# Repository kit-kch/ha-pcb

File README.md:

# KCH Half Adder PCB

This repository contains schematic, layout and BOM for the KCH half adder PCB.
The PCB realizes a half adder using NAND gates, where some of the on-board components are left to be soldered by students as an exercise.

Multiple PCBs can be connected to each other to form full adders or multi-bit carry ripple adders.
In addition to the PCB, we provide detailed documentation explaining the theory involved for both the PCB design and the digital circuit realization.

As the intended target audience is school students and their teachers, documentation is currently only available in German.

## Ordering the PCBs

The initial batch of boards we have successfully used in a workshop has been ordered using JLCPCB's standard assembly service.
We had all the parts assembled, except for the switches and the 74HC00 ICs that are marked as do-not-place in the schematic.
Because of that, both-sided assembly and THT assembly is required.
The files we used to order from JLCPCB can be found in the production folder.

Please note: As the connectors are overlapping, the assembly service needs to add some spacers when paneling the design. Either panel yourself or let the factory know about this requirement.

Please also note that the boards should align when connected together.
PCB edges therefore need to be smooth so mouse bites should not be used.
Make sure to use v-score / v-cut panels instead.

## More Information and Documentation

* Project Website and Documentation: [kch.dev/ha](https://kch.dev/ha)
* Project Schematic: [kch_ha.pdf](kch_ha.pdf)

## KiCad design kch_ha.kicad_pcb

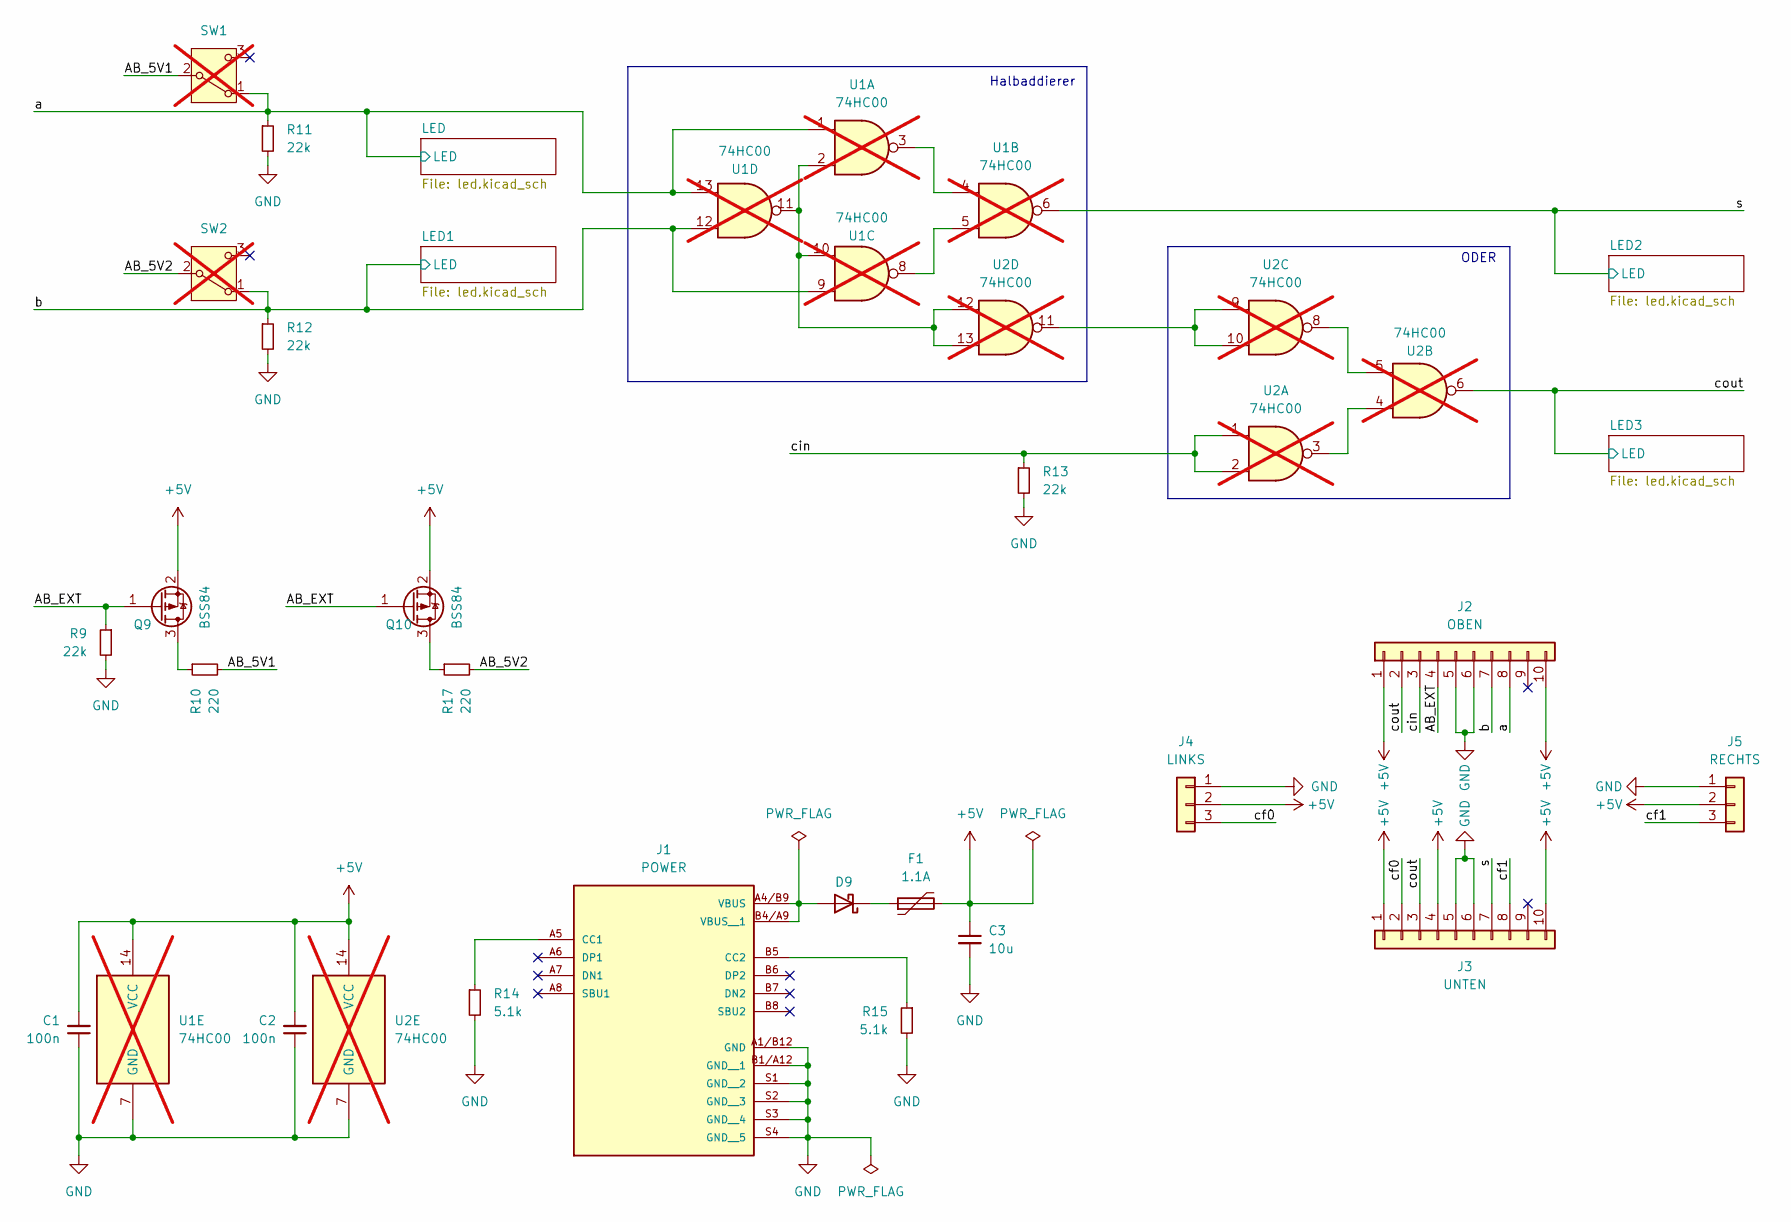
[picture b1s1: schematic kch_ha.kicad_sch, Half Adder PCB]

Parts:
C1, C2: 100n; C_0805_2012Metric; LCSC C476766
C3: 10u; C_0805_2012Metric; LCSC C5137471
D9: D_SMA; LCSC C2844169
F1: 1.1A; FUSER_2016L050MR; MPN 2016L050MR; LCSC C99564
J1: POWER; GCT_USB4110-GF-A_REVB; PARTREV B; LCSC C5143397
J2: OBEN; PinSocket_1x10_P2.54mm_Horizontal; MPN PPTC101LGBN-RC; LCSC C22438151
J3: UNTEN; PinHeader_1x10_P2.54mm_Horizontal; MPN PH1RB-10-UA; LCSC C492418
J4: LINKS; PinHeader_1x03_P2.54mm_Horizontal; MPN PH1RB-03-UA; LCSC C492411
J5: RECHTS; PinSocket_1x03_P2.54mm_Horizontal; MPN PPTC031LGBN-RC; LCSC C22438144
Q9, Q10: BSS84; SOT-23; MPN BSS84P; LCSC C112238
R9, R11, R12, R13: 22k; R_0805_2012Metric; LCSC C139902
R10, R17: 220; R_0805_2012Metric; LCSC C2933537
R14, R15: 5.1k; R_0805_2012Metric; LCSC C2930296
SW1: a; SW_Slide-03_Wuerth-WS-SLTV_10x2.5x6.4_P2.54mm; not fitted
SW2: b; SW_Slide-03_Wuerth-WS-SLTV_10x2.5x6.4_P2.54mm; not fitted
U1, U2: 74HC00; DIP-14_W7.62mm; MPN 74HC00; not fitted

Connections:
+5V: C1.2, C2.2, C3.1, F1.2, J2.1, J2.10, J3.1, J3.4, J3.10, J4.2, J5.2, Q9.2 (S), Q10.2 (S), U1.14 (VCC), U2.14 (VCC); also elsewhere on the board
/AB_5V1: R10.2, SW1.2 (B)
/AB_5V2: R17.2, SW2.2 (B)
/AB_EXT: J2.4, Q9.1 (G), Q10.1 (G), R9.1
/a: J2.8, R11.1, SW1.1 (A), U1.1, U1.13; also elsewhere on the board
/b: J2.7, R12.1, SW2.1 (A), U1.9, U1.12; also elsewhere on the board
/cf0: J3.2, J4.3
/cf1: J3.8, J5.3
/cin: J2.3, R13.1, U2.1, U2.2
/cout: J2.2, J3.3, U2.6; also elsewhere on the board
/s: J3.7, U1.6; also elsewhere on the board
GND: C1.1, C2.1, C3.2, J1.A1/B12 (GND), J1.B1/A12 (GND__1), J1.S1 (GND__2), J1.S2 (GND__3), J1.S3 (GND__4), J1.S4 (GND__5), J2.5, J2.6, J3.5, J3.6, J4.1, J5.1, R9.2, R11.2, R12.2, R13.2, R14.2, R15.2, U1.7 (GND), U2.7 (GND); also elsewhere on the board
unnamed: D9.2 (A), J1.A4/B9 (VBUS), J1.B4/A9 (VBUS__1)
unnamed: D9.1 (K), F1.1
unnamed: J1.A5 (CC1), R14.1
unnamed: J1.B5 (CC2), R15.1
unnamed: Q9.3 (D), R10.1
unnamed: Q10.3 (D), R17.1
unnamed: U1.3, U1.4
unnamed: U1.5, U1.8
unnamed: U1.2, U1.10, U1.11, U2.12, U2.13
unnamed: U2.3, U2.4
unnamed: U2.5, U2.8
unnamed: U2.9, U2.10, U2.11

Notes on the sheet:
Halbaddierer
ODER

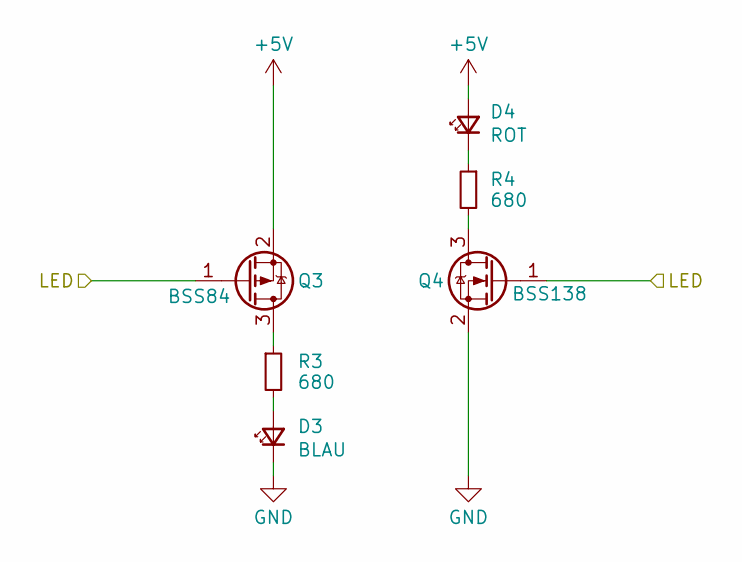
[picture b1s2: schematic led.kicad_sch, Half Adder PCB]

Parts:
D3: BLAU; LED_0805_2012Metric; MPN LTST-C170TBKT; LCSC C98222
D4: ROT; LED_0805_2012Metric; MPN LTST-C170KRKT; LCSC C94868
Q3: BSS84; SOT-23; MPN BSS84P; LCSC C112238
Q4: BSS138; SOT-23; MPN BSS138; LCSC C78284
R3, R4: 680; R_0805_2012Metric; LCSC C17798

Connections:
+5V: D4.2 (A), Q3.2 (S); also elsewhere on the board
/a: Q3.1 (G), Q4.1 (G); also elsewhere on the board
GND: D3.1 (K), Q4.2 (S); also elsewhere on the board
unnamed: D3.2 (A), R3.2
unnamed: D4.1 (K), R4.1
unnamed: Q3.3 (D), R3.1
unnamed: Q4.3 (D), R4.2

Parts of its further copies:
D1, D5, D7: BLAU; LED_0805_2012Metric; MPN LTST-C170TBKT; LCSC C98222
D2, D6, D8: ROT; LED_0805_2012Metric; MPN LTST-C170KRKT; LCSC C94868
Q1, Q5, Q7: BSS84; SOT-23; MPN BSS84P; LCSC C112238
Q2, Q6, Q8: BSS138; SOT-23; MPN BSS138; LCSC C78284
R1, R2, R5, R6, R7, R8: 680; R_0805_2012Metric; LCSC C17798

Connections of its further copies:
+5V: D2.2 (A), D6.2 (A), D8.2 (A), Q1.2 (S), Q5.2 (S), Q7.2 (S); also elsewhere on the board
/b: Q1.1 (G), Q2.1 (G); also elsewhere on the board
/cout: Q7.1 (G), Q8.1 (G); also elsewhere on the board
/s: Q5.1 (G), Q6.1 (G); also elsewhere on the board
GND: D1.1 (K), D5.1 (K), D7.1 (K), Q2.2 (S), Q6.2 (S), Q8.2 (S); also elsewhere on the board
unnamed: D1.2 (A), R1.2
unnamed: D2.1 (K), R2.1
unnamed: D5.2 (A), R5.2
unnamed: D6.1 (K), R6.1
unnamed: D7.2 (A), R7.2
unnamed: D8.1 (K), R8.1
unnamed: Q1.3 (D), R1.1
unnamed: Q2.3 (D), R2.2
unnamed: Q5.3 (D), R5.1
unnamed: Q6.3 (D), R6.2
unnamed: Q7.3 (D), R7.1
unnamed: Q8.3 (D), R8.2

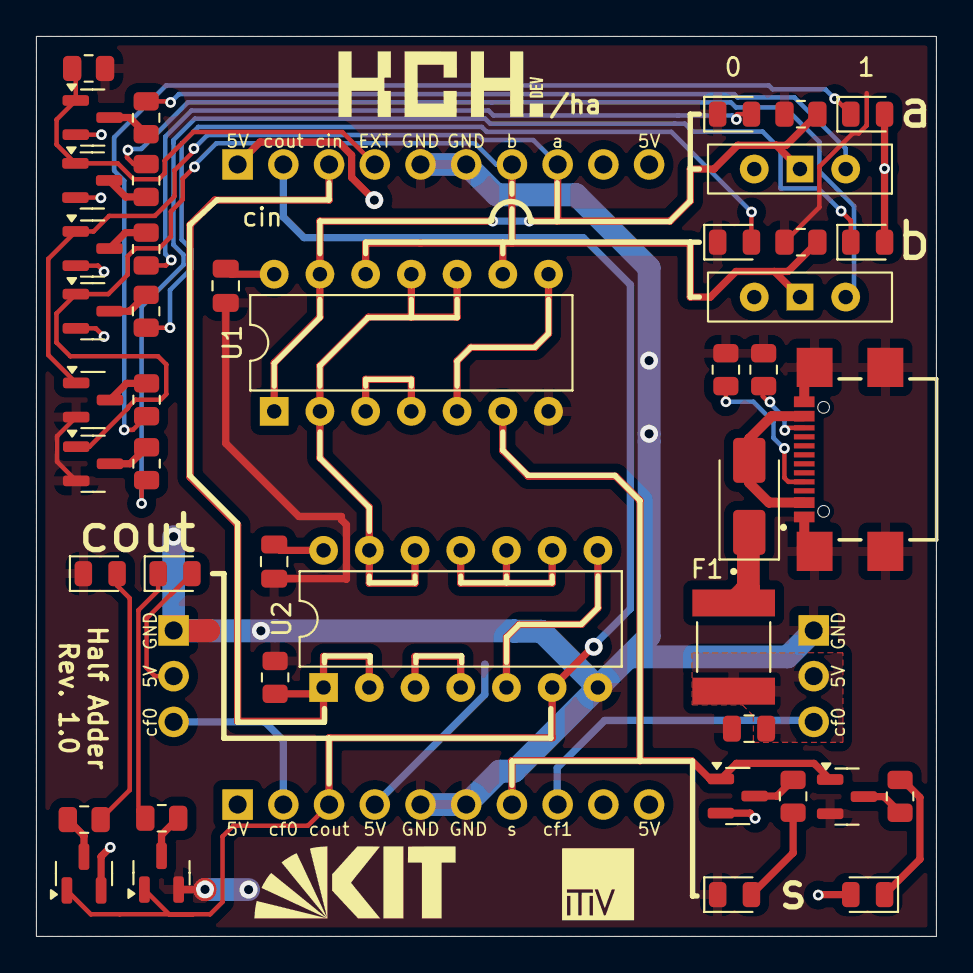
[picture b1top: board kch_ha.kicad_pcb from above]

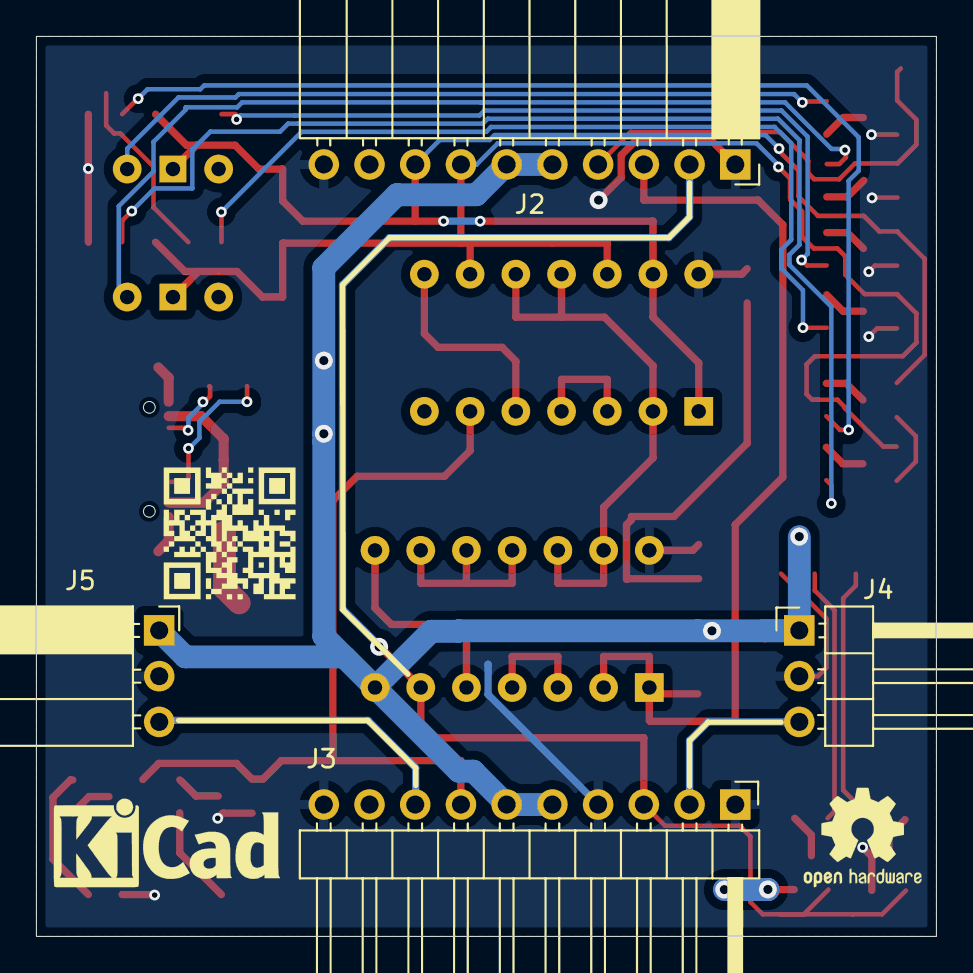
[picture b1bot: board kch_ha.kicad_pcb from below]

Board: 2 copper layers, 50.0 x 50.0 mm, 48 parts (4 on the bottom side), 40 nets.

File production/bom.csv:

Designator,Footprint,Quantity,Value,LCSC Part #
"C1, C2",0805,2,100n,C476766
C3,0805,1,10u,C5137471
"D1, D3, D5, D7",0805,4,BLAU,C98222
"D2, D4, D6, D8",0805,4,ROT,C94868
D9,D_SMA,1,~,C2844169
F1,FUSER_2016L050MR,1,1.1A,C99564
J1,GCT_USB4110-GF-A_REVB,1,POWER,C5143397
J2,PinSocket_1x10_P2.54mm_Horizontal,1,OBEN,C22438151
J3,PinHeader_1x10_P2.54mm_Horizontal,1,UNTEN,C492418
J4,PinHeader_1x03_P2.54mm_Horizontal,1,LINKS,C492411
J5,PinSocket_1x03_P2.54mm_Horizontal,1,RECHTS,C22438144
"Q1, Q10, Q3, Q5, Q7, Q9",SOT-23,6,BSS84, C112238
"Q2, Q4, Q6, Q8",SOT-23,4,BSS138,C78284
"R1, R2, R3, R4, R5, R6, R7, R8",0805,8,680,C17798
"R10, R17",0805,2,220,C2933537
"R11, R12, R13, R9",0805,4,22k,C139902
"R14, R15",0805,2,5.1k,C2930296

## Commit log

2025-05-07 Initial public release
2025-05-08 Rerender schematic.png
